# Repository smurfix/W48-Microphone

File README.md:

# W48-Microphone
Electret microphone as a drop in replacement for the W48 (and other) coal microphone.

derived from https://opppf.de/TelephonMic/index.html

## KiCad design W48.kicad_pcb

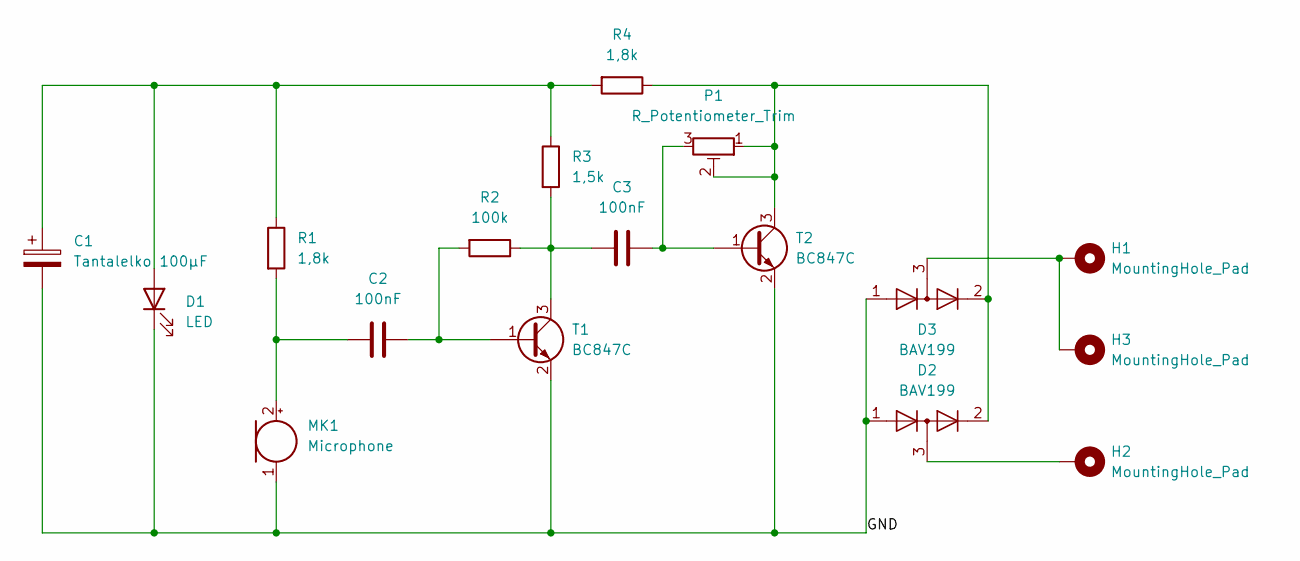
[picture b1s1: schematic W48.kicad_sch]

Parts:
C1: Tantalelko 100µF; CP_EIA-7343-15_Kemet-W
C2, C3: 100nF; C_0805_2012Metric
D1: LED; LED_D3.0mm
D2, D3: BAV199; SOT-23
H1, H2, H3: MountingHole_Pad; MountingHole_3.2mm_M3_DIN965_Pad
MK1: Microphone; LED_D3.0mm
P1: R_Potentiometer_Trim; Potentiometer_ACP_CA6-VSMD_Vertical
R1, R4: 1,8k; R_0805_2012Metric
R2: 100k; R_0805_2012Metric
R3: 1,5k; R_0805_2012Metric
T1, T2: BC847C; SOT-23

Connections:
/GND: C1.2, D1.1 (K), D2.1 (K), D3.1 (K), MK1.1 (-), T1.2 (E), T2.2 (E)
unnamed: C1.1, D1.2 (A), R1.1, R3.1, R4.2
unnamed: D2.2 (A), D3.2 (A), P1.1, P1.2, R4.1, T2.3 (C)
unnamed: D2.3 (K), H2.1
unnamed: D3.3 (K), H1.1, H3.1
unnamed: C2.2, MK1.2 (+), R1.2
unnamed: C2.1, R2.2, T1.1 (B)
unnamed: C3.2, R2.1, R3.2, T1.3 (C)
unnamed: C3.1, P1.3, T2.1 (B)

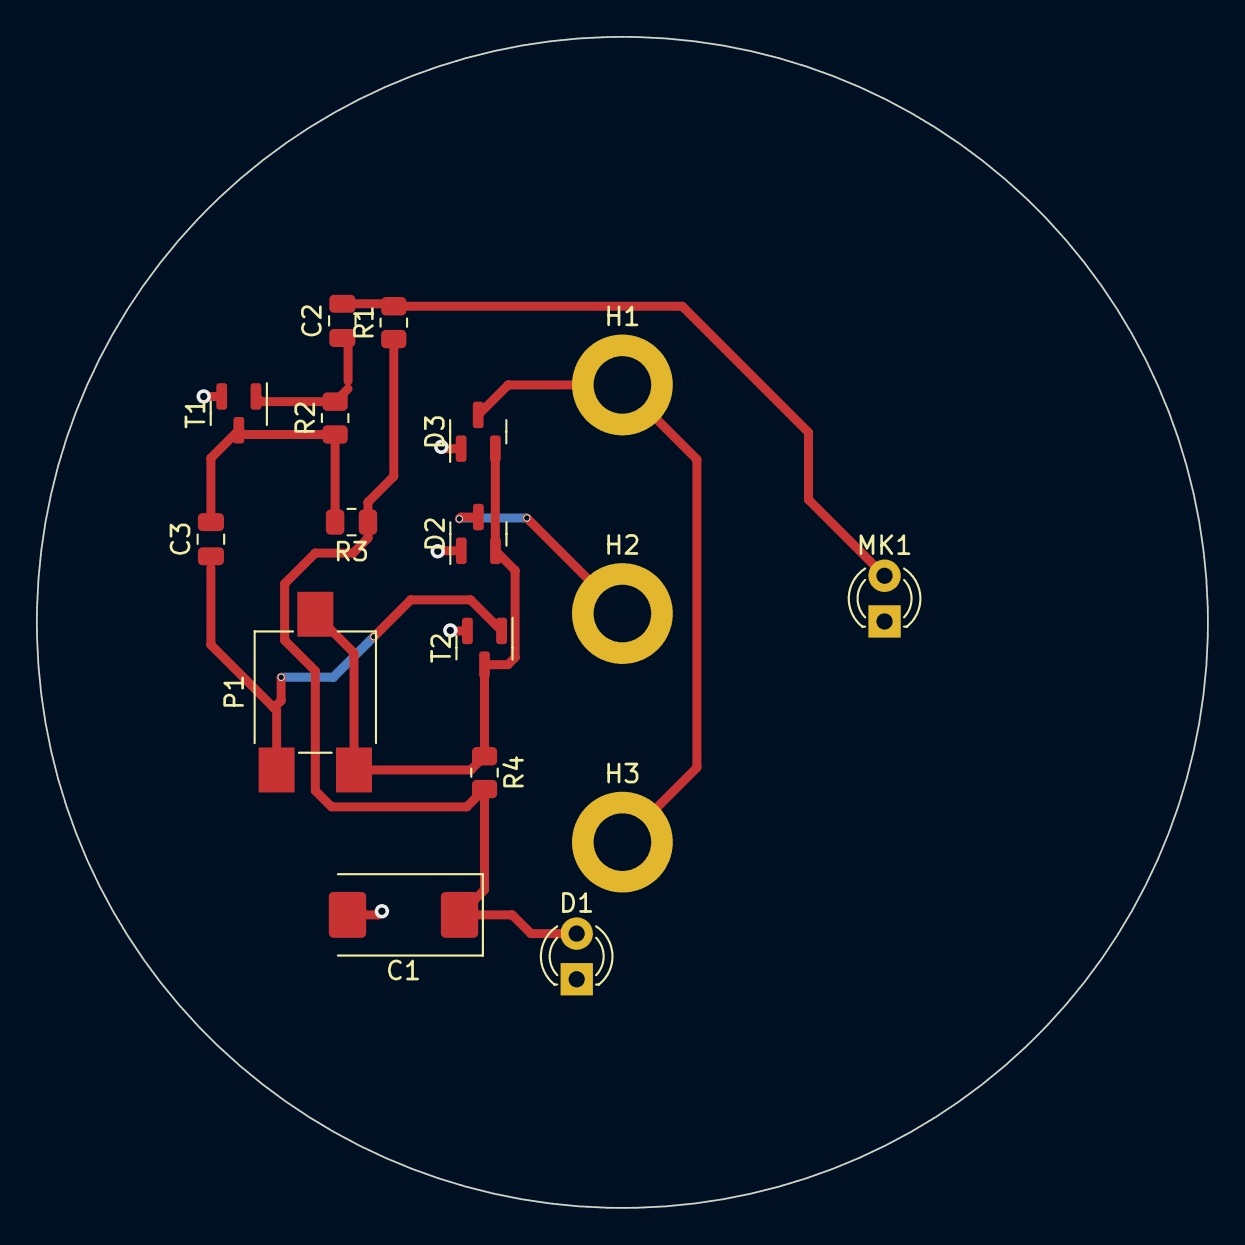
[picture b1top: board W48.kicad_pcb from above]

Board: 2 copper layers, 65.1 x 65.1 mm, 17 parts (0 on the bottom side), 9 nets.

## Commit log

2023-02-15 initial circuit and footprints, missing layout
2023-02-15 Link to circuit source
2023-02-17 layout and gnd layer
2023-02-17 real gnd layer
